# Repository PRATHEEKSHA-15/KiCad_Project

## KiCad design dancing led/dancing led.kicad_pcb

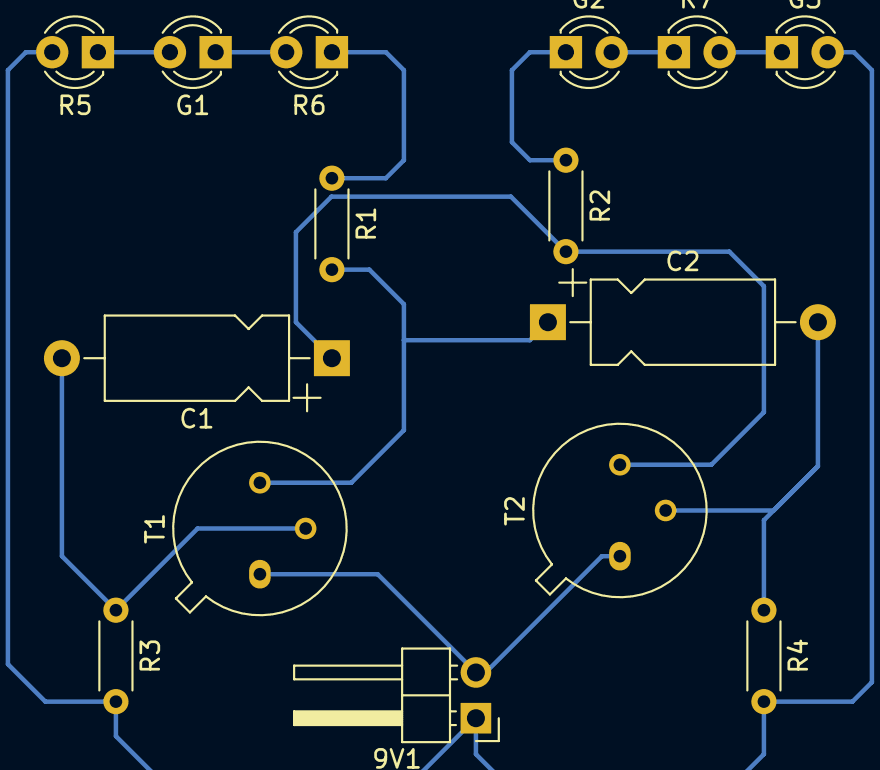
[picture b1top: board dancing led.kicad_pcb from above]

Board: 2 copper layers, 15 parts (0 on the bottom side), 12 nets.

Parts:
9V1: Battery; PinHeader_1x02_P2.54mm_Horizontal
C1, C2: 10uf 40V; CP_Axial_L10.0mm_D4.5mm_P15.00mm_Horizontal
G1: D2; LED_D3.0mm
G2: D4; LED_D3.0mm
G3: G; LED_D3.0mm
R1, R2: 100 ohms; R_Axial_DIN0204_L3.6mm_D1.6mm_P5.08mm_Horizontal
R3, R4: 47K; R_Axial_DIN0204_L3.6mm_D1.6mm_P5.08mm_Horizontal
R5: D1; LED_D3.0mm
R6: D3; LED_D3.0mm
R7: D5; LED_D3.0mm
T1, T2: BC 547; TO-39-3

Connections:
Earth: 9V1.1, G3.2, R3.2, R4.2, R5.2
unnamed: 9V1.2, T1.1, T2.1
unnamed: C1.1, R2.2, T2.3
unnamed: C1.2, R3.1, T1.2
unnamed: C2.1, R1.2, T1.3
unnamed: C2.2, R4.1, T2.2
unnamed: G1.1, R6.2
unnamed: G1.2, R5.1
unnamed: G2.1, R2.1
unnamed: G2.2, R7.1
unnamed: G3.1, R7.2
unnamed: R1.1, R6.1

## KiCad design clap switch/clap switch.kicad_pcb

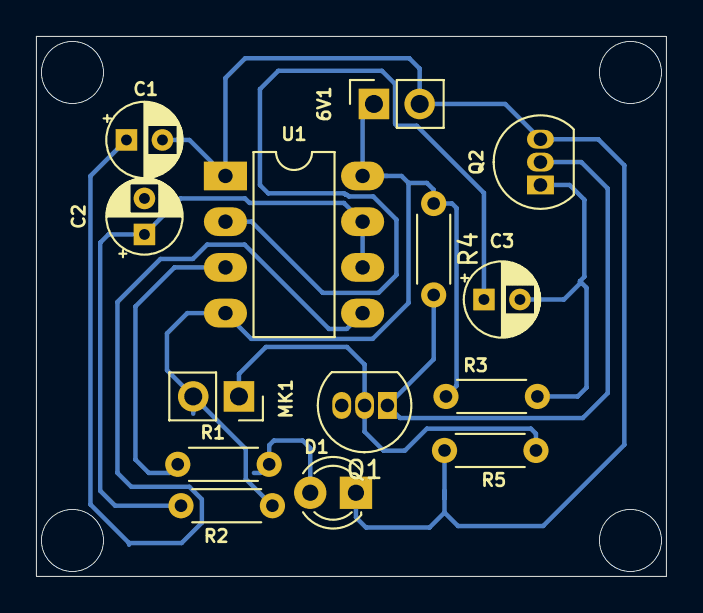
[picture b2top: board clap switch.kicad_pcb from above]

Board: 2 copper layers, 35.0 x 30.0 mm, 14 parts (0 on the bottom side), 10 nets.

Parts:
6V1: Battery; PinSocket_1x02_P2.54mm_Vertical
C1, C3: 0.1uf; CP_Radial_D4.0mm_P2.00mm
C2: 100uf; CP_Radial_D4.0mm_P2.00mm
D1: LED; LED_D3.0mm
MK1: Microphone_Condenser; PinSocket_1x02_P2.54mm_Vertical
Q1, Q2: BC547; TO-92_Inline
R1: 330; R_Axial_DIN0204_L3.6mm_D1.6mm_P5.08mm_Horizontal
R2: 10K; R_Axial_DIN0204_L3.6mm_D1.6mm_P5.08mm_Horizontal
R3: 470; R_Axial_DIN0204_L3.6mm_D1.6mm_P5.08mm_Horizontal
R4: 1K; R_Axial_DIN0204_L3.6mm_D1.6mm_P5.08mm_Horizontal
R5: 4.7K; R_Axial_DIN0204_L3.6mm_D1.6mm_P5.08mm_Horizontal
U1: ICM7555xB; DIP-8_W7.62mm_LongPads

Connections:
Earth: 6V1.2, C1.2, C2.2, D1.1, Q1.3, Q2.3, R5.2, U1.1
unnamed: 6V1.1, MK1.2, R2.1, R3.1, R4.1, U1.4, U1.8
unnamed: C1.1, U1.5
unnamed: C2.1, R2.2, U1.6, U1.7
unnamed: C3.1, U1.2
unnamed: C3.2, Q2.1, R3.2
unnamed: D1.2, R1.2
unnamed: MK1.1, Q1.2, R5.1
unnamed: Q1.1, Q2.2, R4.2
unnamed: R1.1, U1.3

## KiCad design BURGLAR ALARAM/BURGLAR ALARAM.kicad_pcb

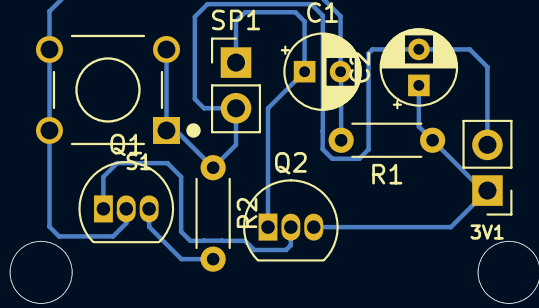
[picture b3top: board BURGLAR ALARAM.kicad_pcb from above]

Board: 2 copper layers, 9 parts (0 on the bottom side), 6 nets.

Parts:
3V1: Battery; PinHeader_1x02_P2.54mm_Vertical
C1: 0.01uf; CP_Radial_D4.0mm_P2.00mm
C2: 100uf; CP_Radial_D4.0mm_P2.00mm
Q1: BC547; TO-92_Inline
Q2: BC327; TO-92_Inline
R1: 330k; R_Axial_DIN0204_L3.6mm_D1.6mm_P5.08mm_Horizontal
R2: 100 ohm; R_Axial_DIN0204_L3.6mm_D1.6mm_P5.08mm_Horizontal
S1: FSM8JH; SW_FSM8JH
SP1: 100 ohm; PinHeader_1x02_P2.54mm_Vertical

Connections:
Earth: 3V1.2, C2.2, R2.1, S1.1, S1.2, SP1.2
unnamed: 3V1.1, C2.1, Q2.3, R1.1
unnamed: C1.1, Q2.1, SP1.1
unnamed: C1.2, Q1.2, R1.2, S1.3, S1.4
unnamed: Q1.1, Q2.2
unnamed: Q1.3, R2.2
